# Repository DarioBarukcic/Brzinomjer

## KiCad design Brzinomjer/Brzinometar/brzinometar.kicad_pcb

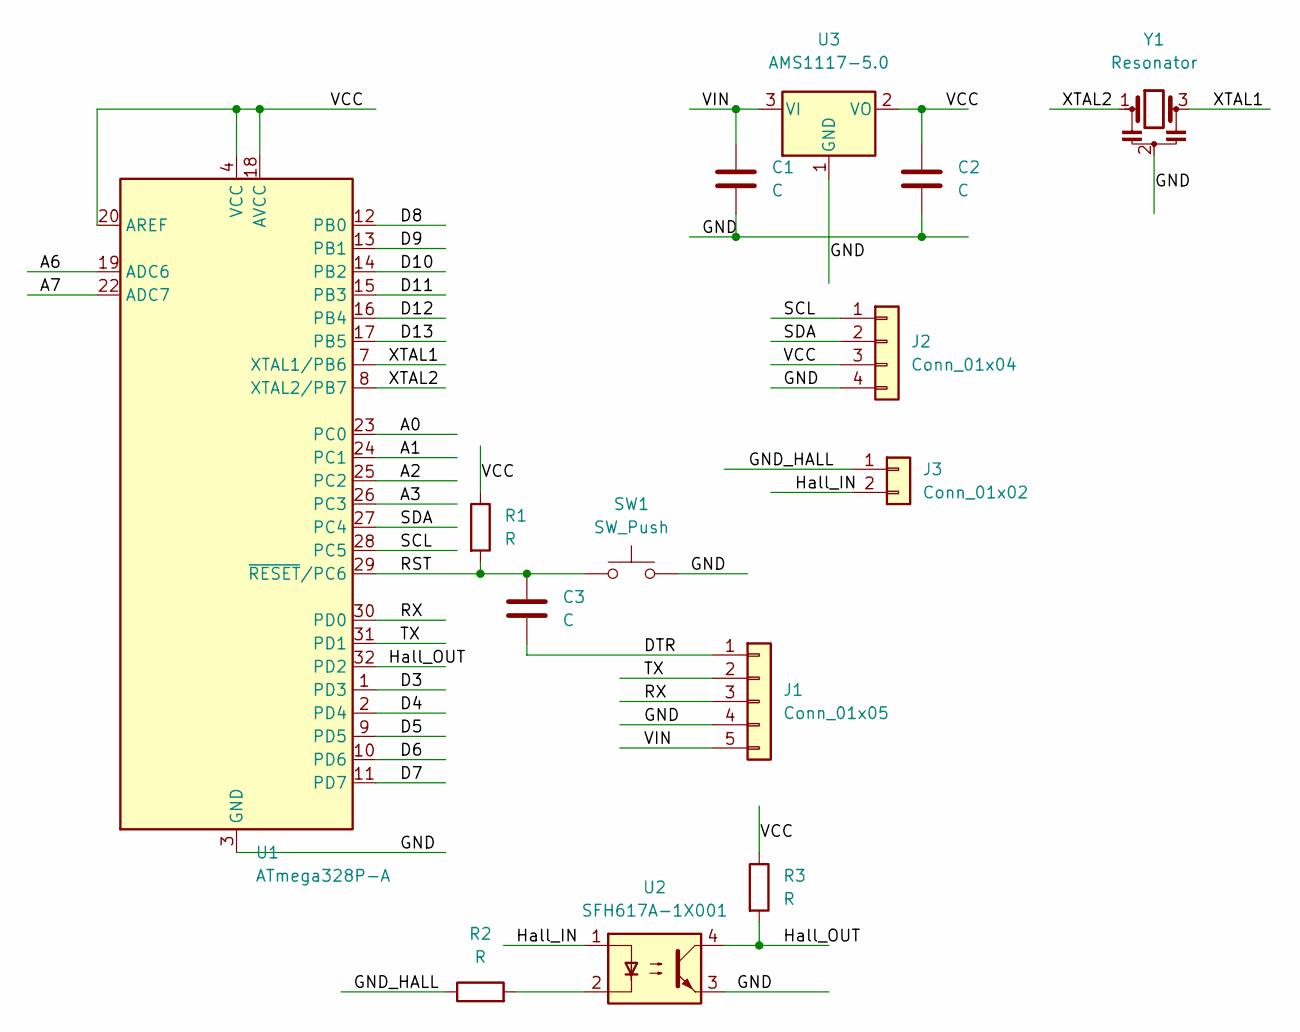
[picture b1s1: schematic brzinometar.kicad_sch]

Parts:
C1, C2, C3: C; C_0805_2012Metric
J1: Conn_01x05; PinSocket_1x05_P2.54mm_Vertical
J2: Conn_01x04; PinSocket_1x04_P2.54mm_Horizontal
J3: Conn_01x02; PinSocket_1x02_P2.54mm_Vertical
R1, R2, R3: R; R_0805_2012Metric
SW1: SW_Push; SW_SPST_CK_RS282G05A3
U1: ATmega328P-A; TQFP-32_7x7mm_P0.8mm
U2: SFH617A-1X001; DIP-4_W7.62mm
U3: AMS1117-5.0; SOT-223-3_TabPin2
Y1: Resonator; Resonator_SMD_Murata_CSTxExxV-3Pin_3.0x1.1mm

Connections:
/A0: U1.23 (PC0)
/A1: U1.24 (PC1)
/A2: U1.25 (PC2)
/A3: U1.26 (PC3)
/A6: U1.19 (ADC6)
/A7: U1.22 (ADC7)
/D3: U1.1 (PD3)
/D4: U1.2 (PD4)
/D5: U1.9 (PD5)
/D6: U1.10 (PD6)
/D7: U1.11 (PD7)
/D8: U1.12 (PB0)
/D9: U1.13 (PB1)
/D10: U1.14 (PB2)
/D11: U1.15 (PB3)
/D12: U1.16 (PB4)
/D13: U1.17 (PB5)
/DTR: C3.2, J1.1
/GND: C1.2, C2.2, J1.4, J2.4, SW1.2, U1.3 (GND), U1.5 (GND), U1.21 (GND), U2.3, U3.1 (GND), Y1.2
/GND_HALL: J3.1, R2.1
/Hall_IN: J3.2, U2.1
/Hall_OUT: R3.2, U1.32 (PD2), U2.4
/RST: C3.1, R1.2, SW1.1, U1.29 (~RESET/PC6)
/RX: J1.3, U1.30 (PD0)
/SCL: J2.1, U1.28 (PC5)
/SDA: J2.2, U1.27 (PC4)
/TX: J1.2, U1.31 (PD1)
/VCC: C2.1, J2.3, R1.1, R3.1, U1.4 (VCC), U1.6 (VCC), U1.18 (AVCC), U1.20 (AREF), U3.2 (VO)
/VIN: C1.1, J1.5, U3.3 (VI)
/XTAL1: U1.7 (XTAL1/PB6), Y1.3
/XTAL2: U1.8 (XTAL2/PB7), Y1.1
unnamed: R2.2, U2.2

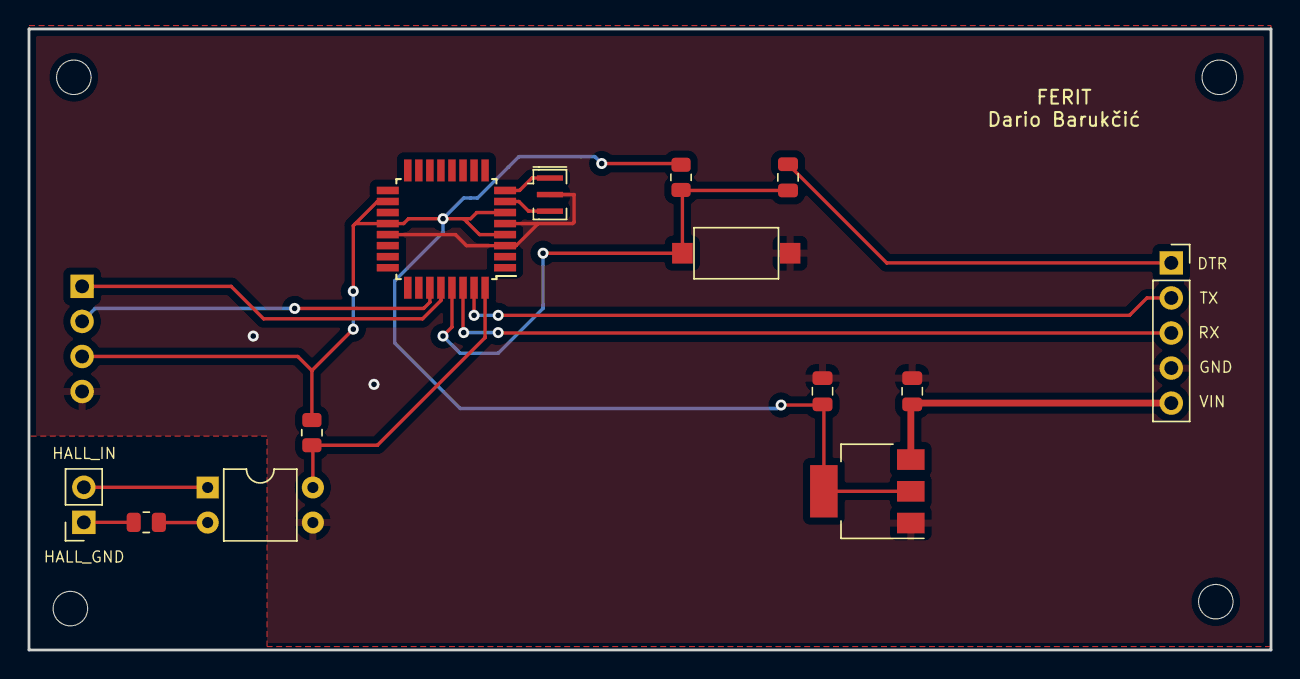
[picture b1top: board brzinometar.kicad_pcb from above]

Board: 2 copper layers, 90.0 x 45.0 mm, 14 parts (1 on the bottom side), 15 nets.
